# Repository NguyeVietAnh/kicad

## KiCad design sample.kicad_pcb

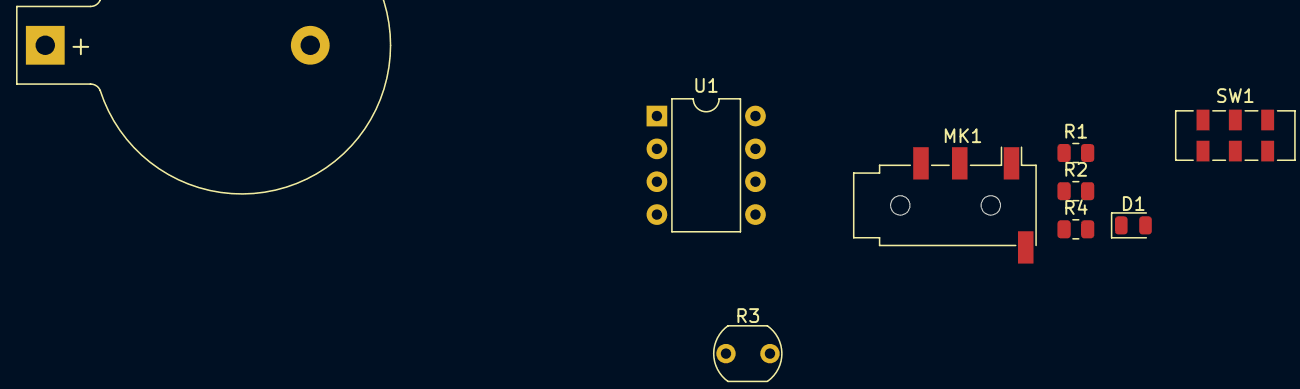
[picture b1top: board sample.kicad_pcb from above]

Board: 2 copper layers, 9 parts (0 on the bottom side), 7 nets, no tracks yet.

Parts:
BT1: 3.3V Battery; BatteryHolder_Keystone_103_1x20mm
D1: LED; LED_0805_2012Metric
MK1: Microphone_Condenser; Jack_3.5mm_PJ320D_Horizontal
R1, R2: R; R_0805_2012Metric
R3: LDR07; R_LDR_5.1x4.3mm_P3.4mm_Vertical
R4: 5.6k; R_0805_2012Metric
SW1: SW_DPDT_x2; SW_DPDT_CK_JS202011JCQN
U1: ATtiny85V-10P; DIP-8_W7.62mm

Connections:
+3.3V: BT1.1 (+), R2.1, R4.1, U1.8 (VCC)
/LDR: R2.2, R3.1, U1.7 (PB2)
/LED: D1.2 (A), U1.6 (PB1)
/MIC: R4.2, U1.2 (XTAL1/PB3)
GND: R1.2, R3.2, SW1.2 (B), U1.4 (GND)
unnamed: BT1.2 (-), SW1.3 (C)
unnamed: D1.1 (K), R1.1
